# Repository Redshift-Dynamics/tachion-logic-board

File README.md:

The project is in heavy development, use at your own risk

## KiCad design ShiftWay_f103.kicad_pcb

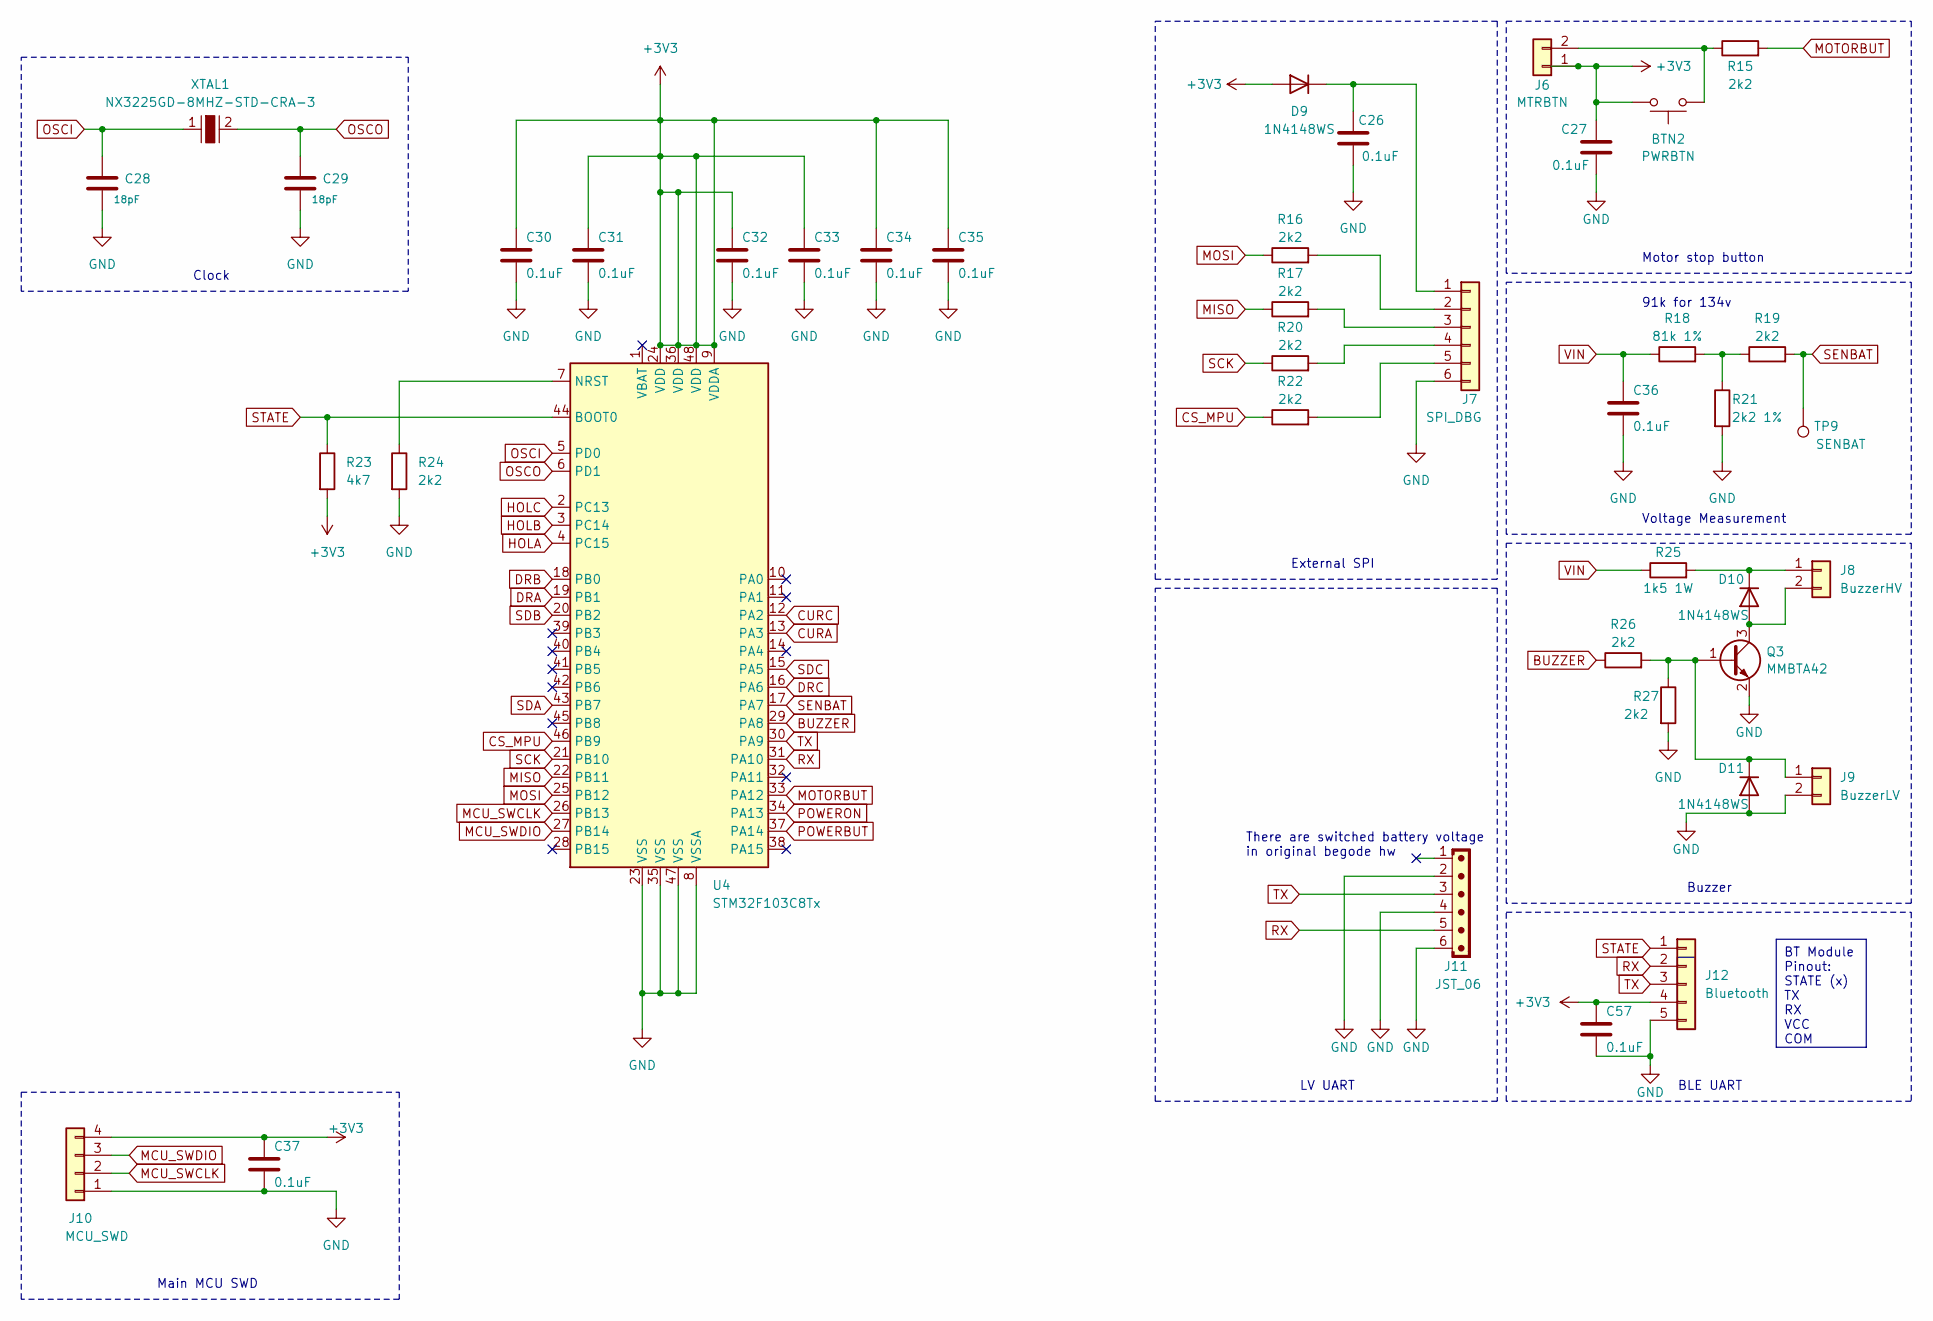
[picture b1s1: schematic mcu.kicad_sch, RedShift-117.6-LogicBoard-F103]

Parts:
BTN2: PWRBTN; SW_SPST_SKQG_WithoutStem
C26, C27, C30, C31, C32, C33, C34, C35, C37, C57: 0.1uF; C_0603_1608Metric_Pad1.08x0.95mm_HandSolder
C28, C29: 18pF; C_0402_1005Metric_Pad0.74x0.62mm_HandSolder
C36: 0.1uF; C_0805_2012Metric_Pad1.18x1.45mm_HandSolder
D9, D10, D11: 1N4148WS; D_SOD-323
J6: MTRBTN; JST_XH_B2B-XH-A_1x02_P2.50mm_Vertical
J7: SPI_DBG; PinSocket_1x07_P1.27mm_Vertical
J8: BuzzerHV; JST_XH_B2B-XH-A_1x02_P2.50mm_Vertical
J9: BuzzerLV; JST_XH_B2B-XH-A_1x02_P2.50mm_Vertical
J10: MCU_SWD; PinSocket_1x04_P2.54mm_Vertical
J11: JST_06; JST_EH_B6B-EH-A_1x06_P2.50mm_Vertical
J12: Bluetooth; PinSocket_1x05_P2.54mm_Vertical
Q3: MMBTA42; SOT-23
R15, R16, R17, R19, R20, R22, R24, R26, R27: 2k2; R_0603_1608Metric_Pad0.98x0.95mm_HandSolder
R18: 81k 1%; R_0805_2012Metric_Pad1.20x1.40mm_HandSolder
R21: 2k2 1%; R_0805_2012Metric_Pad1.20x1.40mm_HandSolder
R23: 4k7; R_0603_1608Metric_Pad0.98x0.95mm_HandSolder
R25: 1k5 1W; R_2010_5025Metric_Pad1.40x2.65mm_HandSolder
TP9: SENBAT; TestPoint_Pad_D2.0mm
U4: STM32F103C8Tx; LQFP-48_7x7mm_P0.5mm
XTAL1: NX3225GD-8MHZ-STD-CRA-3; SMD-2_3.2x2.5mm; MPN NX3225GD-8MHZ-STD-CRA-3; Digi-Key_PN 644-1178-1-ND

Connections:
+3V3: BTN2.2, C27.1, C30.1, C31.1, C32.1, C33.1, C34.1, C35.1, C37.1, C57.1, D9.2 (A), J6.1, J10.4, J12.4, R23.2, U4.9 (VDDA), U4.24 (VDD), U4.36 (VDD), U4.48 (VDD); also elsewhere on the board
BUZZER: R26.1, U4.29 (PA8)
CS_MPU: R22.1, U4.46 (PB9); also elsewhere on the board
CURA: U4.13 (PA3); also elsewhere on the board
CURC: U4.12 (PA2); also elsewhere on the board
DRA: U4.19 (PB1); also elsewhere on the board
DRB: U4.18 (PB0); also elsewhere on the board
DRC: U4.16 (PA6); also elsewhere on the board
GND: C26.2, C27.2, C28.2, C29.2, C30.2, C31.2, C32.2, C33.2, C34.2, C35.2, C36.2, C37.2, C57.2, D11.2 (A), J7.6, J9.2, J10.1, J11.2, J11.4, J11.6, J12.5, Q3.2 (E), R21.2, R24.2, R27.2, U4.8 (VSSA), U4.23 (VSS), U4.35 (VSS), U4.47 (VSS); also elsewhere on the board
HOLA: U4.4 (PC15); also elsewhere on the board
HOLB: U4.3 (PC14); also elsewhere on the board
HOLC: U4.2 (PC13); also elsewhere on the board
MCU_SWCLK: J10.2, U4.26 (PB13)
MCU_SWDIO: J10.3, U4.27 (PB14)
MISO: R17.1, U4.22 (PB11); also elsewhere on the board
MOSI: R16.1, U4.25 (PB12); also elsewhere on the board
MOTORBUT: R15.2, U4.33 (PA12)
unnamed: C26.1, D9.1 (K), J7.1
unnamed: D10.2 (A), J8.2, Q3.3 (C)
unnamed: D10.1 (K), J8.1, R25.2
unnamed: D11.1 (K), J9.1, Q3.1 (B), R26.2, R27.1
unnamed: BTN2.1, J6.2, R15.1
unnamed: J7.2, R16.2
unnamed: J7.3, R17.2
unnamed: J7.4, R20.2
unnamed: J7.5, R22.2
unnamed: R18.2, R19.1, R21.1
unnamed: R24.1, U4.7 (NRST)
OSCI: C28.1, U4.5 (PD0), XTAL1.1
OSCO: C29.1, U4.6 (PD1), XTAL1.2
POWERBUT: U4.37 (PA14); also elsewhere on the board
POWERON: U4.34 (PA13); also elsewhere on the board
RX: J11.5, J12.2, U4.31 (PA10)
SCK: R20.1, U4.21 (PB10); also elsewhere on the board
SDA: U4.43 (PB7); also elsewhere on the board
SDB: U4.20 (PB2); also elsewhere on the board
SDC: U4.15 (PA5); also elsewhere on the board
SENBAT: R19.2, TP9.1, U4.17 (PA7)
STATE: J12.1, R23.1, U4.44 (BOOT0)
TX: J11.3, J12.3, U4.30 (PA9)
VIN: C36.1, R18.1, R25.1; also elsewhere on the board

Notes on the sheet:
BT Module Pinout: STATE (x) TX RX VCC COM
Motor stop button
Clock
External SPI
Main MCU SWD
Buzzer
BLE UART
91k for 134v
Voltage Measurement
There are switched battery voltage in original begode hw
LV UART

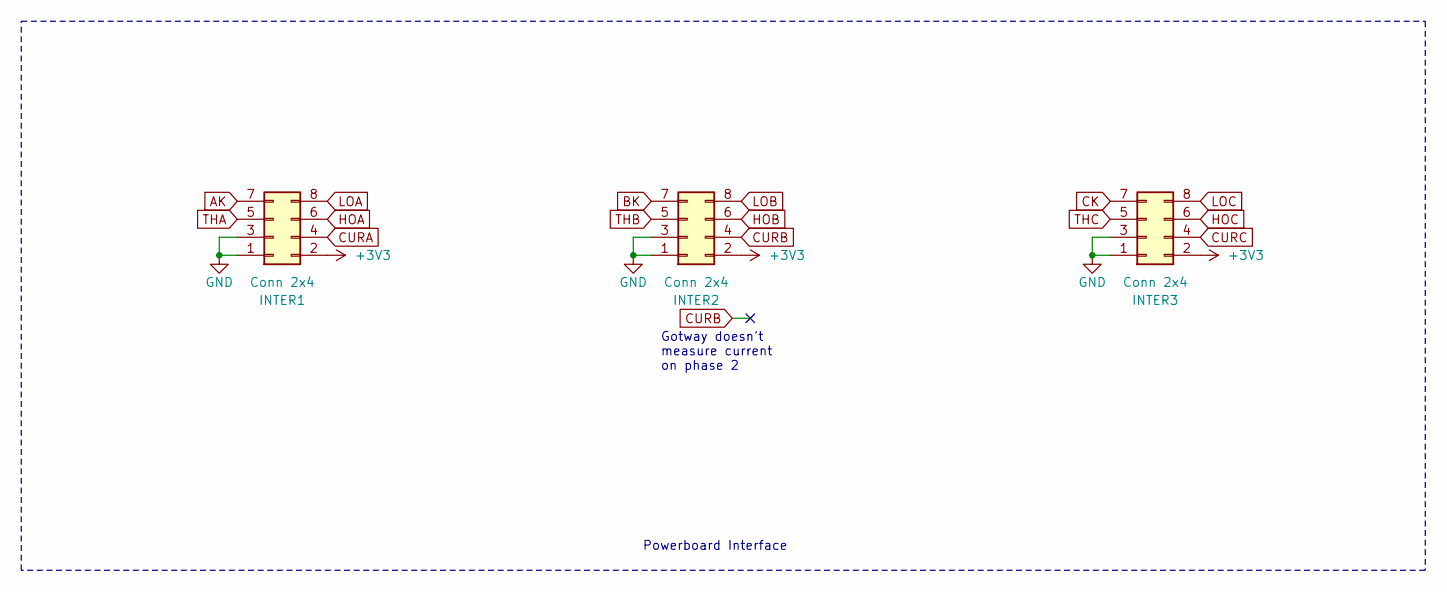
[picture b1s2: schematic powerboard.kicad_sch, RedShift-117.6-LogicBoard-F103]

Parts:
INTER1, INTER2, INTER3: Conn 2x4; PinHeader_2x04_P2.54mm_Vertical

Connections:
+3V3: INTER1.2, INTER2.2, INTER3.2; also elsewhere on the board
AK: INTER1.7; also elsewhere on the board
BK: INTER2.7; also elsewhere on the board
CK: INTER3.7; also elsewhere on the board
CURA: INTER1.4; also elsewhere on the board
CURB: INTER2.4
CURC: INTER3.4; also elsewhere on the board
GND: INTER1.1, INTER1.3, INTER2.1, INTER2.3, INTER3.1, INTER3.3; also elsewhere on the board
HOA: INTER1.6; also elsewhere on the board
HOB: INTER2.6; also elsewhere on the board
HOC: INTER3.6; also elsewhere on the board
LOA: INTER1.8; also elsewhere on the board
LOB: INTER2.8; also elsewhere on the board
LOC: INTER3.8; also elsewhere on the board
THA: INTER1.5
THB: INTER2.5
THC: INTER3.5

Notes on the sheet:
Gotway doesn't measure current on phase 2
Powerboard Interface

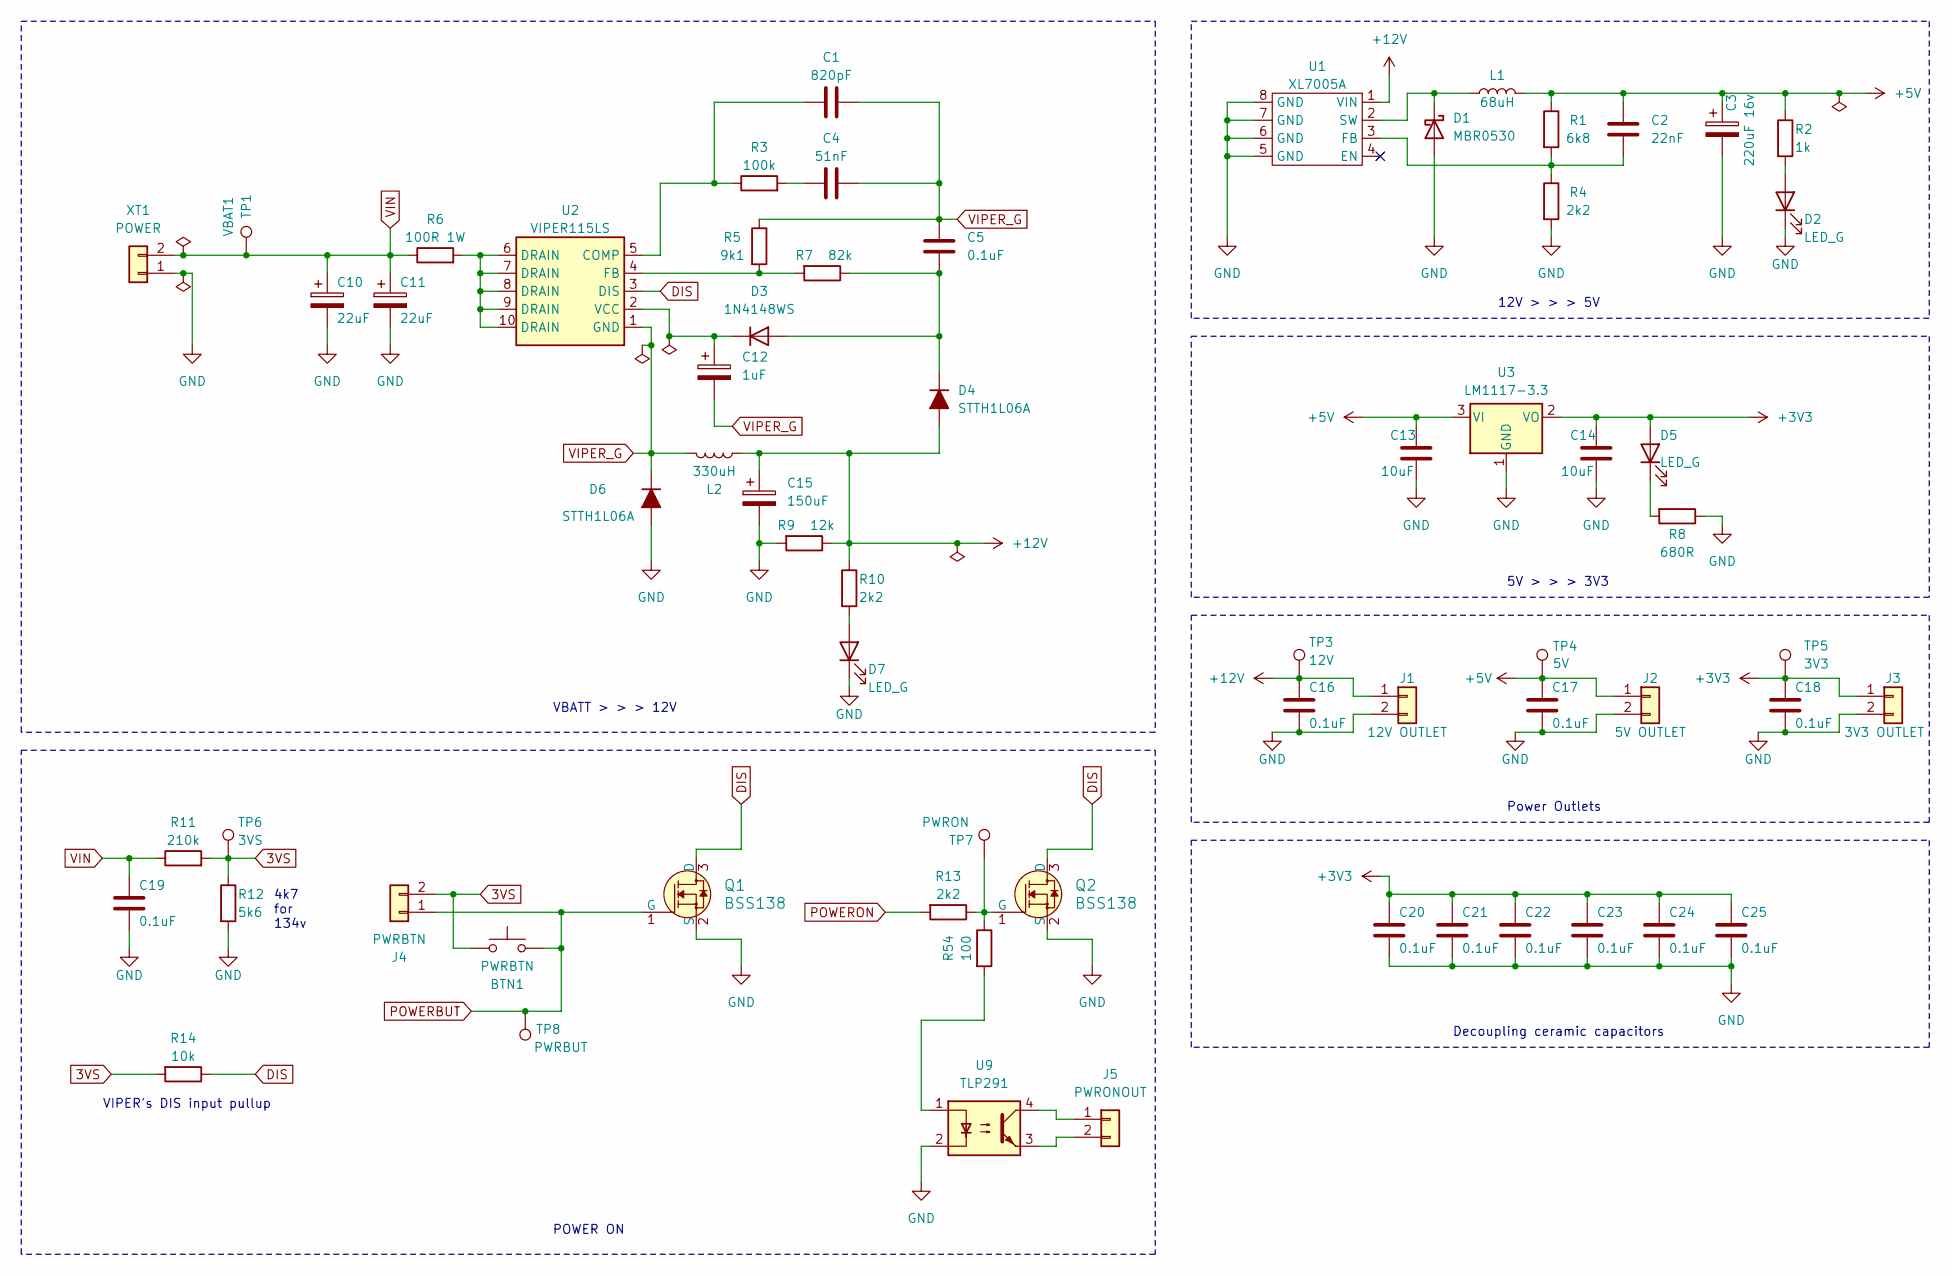
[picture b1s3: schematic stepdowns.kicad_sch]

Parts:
BTN1: PWRBTN; SW_SPST_SKQG_WithoutStem
C1: 820pF; C_0603_1608Metric_Pad1.08x0.95mm_HandSolder
C2: 22nF; C_0603_1608Metric_Pad1.08x0.95mm_HandSolder
C3: 220uF 16v; CP_Elec_6.3x7.7
C4: 51nF; C_0603_1608Metric_Pad1.08x0.95mm_HandSolder
C5, C16, C17, C18, C20, C21, C22, C23, C24, C25: 0.1uF; C_0603_1608Metric_Pad1.08x0.95mm_HandSolder
C10, C11: 22uF; CP_Elec_10x10
C12: 1uF; CP_Elec_10x10
C13, C14: 10uF; C_0603_1608Metric_Pad1.08x0.95mm_HandSolder
C15: 150uF; CP_Elec_10x10
C19: 0.1uF; C_0805_2012Metric_Pad1.18x1.45mm_HandSolder
D1: MBR0530; D_SOD-123
D2, D5, D7: LED_G; LED_0603_1608Metric
D3: 1N4148WS; D_SOD-323
D4, D6: STTH1L06A; D_SMA_Handsoldering
J1: 12V OUTLET; JST_XH_B2B-XH-A_1x02_P2.50mm_Vertical
J2: 5V OUTLET; JST_XH_B2B-XH-A_1x02_P2.50mm_Vertical
J3: 3V3 OUTLET; JST_XH_B2B-XH-A_1x02_P2.50mm_Vertical
J4: PWRBTN; JST_XH_B2B-XH-A_1x02_P2.50mm_Vertical
J5: PWRONOUT; JST_XH_B2B-XH-A_1x02_P2.50mm_Vertical
L1: 68uH; L_Bourns_SRP7028A_7.3x6.6mm
L2: 330uH; L_Bourns_SRR1208_12.7x12.7mm
Q1, Q2: BSS138; SOT-23-3; MPN BSS138; Digi-Key_PN BSS138CT-ND
R1: 6k8; R_0603_1608Metric_Pad0.98x0.95mm_HandSolder
R2: 1k; R_0603_1608Metric_Pad0.98x0.95mm_HandSolder
R3: 100k; R_0603_1608Metric_Pad0.98x0.95mm_HandSolder
R4, R10, R13: 2k2; R_0603_1608Metric_Pad0.98x0.95mm_HandSolder
R5: 9k1; R_0603_1608Metric_Pad0.98x0.95mm_HandSolder
R6: 100R 1W; R_2010_5025Metric_Pad1.40x2.65mm_HandSolder
R7: 82k; R_0603_1608Metric_Pad0.98x0.95mm_HandSolder
R8: 680R; R_0603_1608Metric_Pad0.98x0.95mm_HandSolder
R9: 12k; R_0603_1608Metric_Pad0.98x0.95mm_HandSolder
R11: 210k; R_0805_2012Metric_Pad1.20x1.40mm_HandSolder
R12: 5k6; R_0805_2012Metric_Pad1.20x1.40mm_HandSolder
R14: 10k; R_0603_1608Metric_Pad0.98x0.95mm_HandSolder
R54: 100; R_0603_1608Metric_Pad0.98x0.95mm_HandSolder
TP1: VBAT1; TestPoint_Pad_D2.0mm
TP3: 12V; TestPoint_Pad_D2.0mm
TP4: 5V; TestPoint_Pad_D2.0mm
TP5: 3V3; TestPoint_Pad_D2.0mm
TP6: 3VS; TestPoint_Pad_D2.0mm
TP7: PWRON; TestPoint_Pad_D2.0mm
TP8: PWRBUT; TestPoint_Pad_D2.0mm
U1: XL7005A; SOP-8_3.9x4.9mm_P1.27mm
U2: VIPER115LS; SOIC100P600X175-10N
U3: LM1117-3.3; SOT-223
U9: TLP291; SOIC-4_4.55x2.6mm_P1.27mm
XT1: POWER; AMASS_XT30PW-M_1x02_P2.50mm_Horizontal

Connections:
3VS: BTN1.1, J4.2, R11.2, R12.1, R14.2, TP6.1
+3V3: C14.1, C18.1, C20.1, C21.1, C22.1, C23.1, C24.1, C25.1, D5.2 (A), J3.1, TP5.1, U3.2 (VO); also elsewhere on the board
+5V: C2.1, C3.1, C13.1, C17.1, J2.1, L1.2, R1.1, R2.1, TP4.1, U3.3 (VI); also elsewhere on the board
+12V: C15.1, C16.1, D4.2 (A), J1.1, L2.2, R9.1, R10.1, TP3.1, U1.1 (VIN); also elsewhere on the board
DIS: Q1.3 (D), Q2.3 (D), R14.1, U2.3 (DIS)
GND: C3.2, C10.2, C11.2, C13.2, C14.2, C15.2, C16.2, C17.2, C18.2, C19.2, C20.2, C21.2, C22.2, C23.2, C24.2, C25.2, D1.2 (A), D2.1 (K), D6.2 (A), D7.1 (K), J1.2, J2.2, J3.2, Q1.2 (S), Q2.2 (S), R4.2, R8.1, R9.2, R12.2, U1.5 (GND), U1.6 (GND), U1.7 (GND), U1.8 (GND), U3.1 (GND), U9.2, XT1.1; also elsewhere on the board
unnamed: C4.1, R3.2
unnamed: D1.1 (K), L1.1, U1.2 (SW)
unnamed: D2.2 (A), R2.2
unnamed: C5.1, D3.2 (A), D4.1 (K), R7.1
unnamed: C12.1, D3.1 (K), U2.2 (VCC)
unnamed: D5.1 (K), R8.2
unnamed: D7.2 (A), R10.2
unnamed: J5.1, U9.4
unnamed: J5.2, U9.3
unnamed: Q2.1 (G), R13.1, R54.1, TP7.1
unnamed: R6.2, U2.6 (DRAIN), U2.7 (DRAIN), U2.8 (DRAIN), U2.9 (DRAIN), U2.10 (DRAIN)
unnamed: R54.2, U9.1
unnamed: C2.2, R1.2, R4.1, U1.3 (FB)
unnamed: C1.1, R3.1, U2.5 (COMP)
unnamed: R5.2, R7.2, U2.4 (FB)
POWERBUT: BTN1.2, J4.1, Q1.1 (G), TP8.1; also elsewhere on the board
POWERON: R13.2; also elsewhere on the board
VIN: C10.1, C11.1, C19.1, R6.1, R11.1, TP1.1, XT1.2; also elsewhere on the board
VIPER_G: C1.2, C4.2, C5.2, C12.2, D6.1 (K), L2.1, R5.1, U2.1 (GND)

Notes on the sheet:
Decoupling ceramic capacitors
VBATT > > > 12V
5V > > > 3V3
4k7 for 134v
Power Outlets
12V > > > 5V
POWER ON
VIPER's DIS input pullup

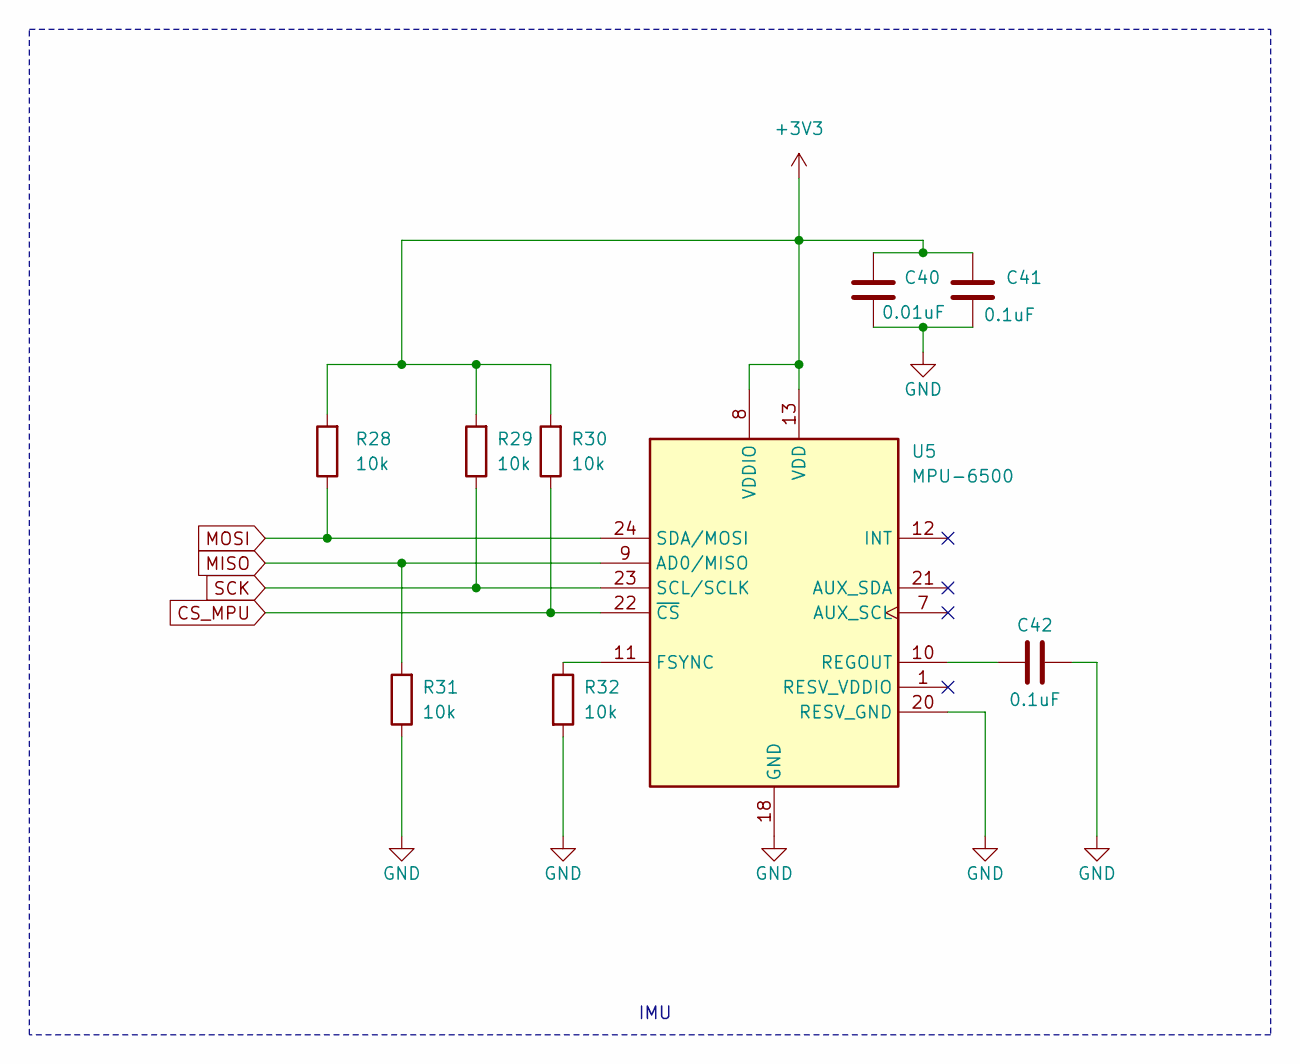
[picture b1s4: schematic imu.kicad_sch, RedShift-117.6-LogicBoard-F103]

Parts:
C40: 0.01uF; C_0603_1608Metric_Pad1.08x0.95mm_HandSolder
C41, C42: 0.1uF; C_0603_1608Metric_Pad1.08x0.95mm_HandSolder
R28, R29, R30, R31, R32: 10k; R_0603_1608Metric_Pad0.98x0.95mm_HandSolder
U5: MPU-6500; InvenSense_QFN-24_3x3mm_P0.4mm

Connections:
+3V3: C40.1, C41.1, R28.2, R29.2, R30.2, U5.8 (VDDIO), U5.13 (VDD); also elsewhere on the board
CS_MPU: R30.1, U5.22 (~CS); also elsewhere on the board
GND: C40.2, C41.2, C42.1, R31.1, R32.2, U5.18 (GND), U5.20 (RESV_GND); also elsewhere on the board
MISO: R31.2, U5.9 (AD0/MISO); also elsewhere on the board
MOSI: R28.1, U5.24 (SDA/MOSI); also elsewhere on the board
unnamed: R32.1, U5.11 (FSYNC)
unnamed: C42.2, U5.10 (REGOUT)
SCK: R29.1, U5.23 (SCL/SCLK); also elsewhere on the board

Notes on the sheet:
IMU

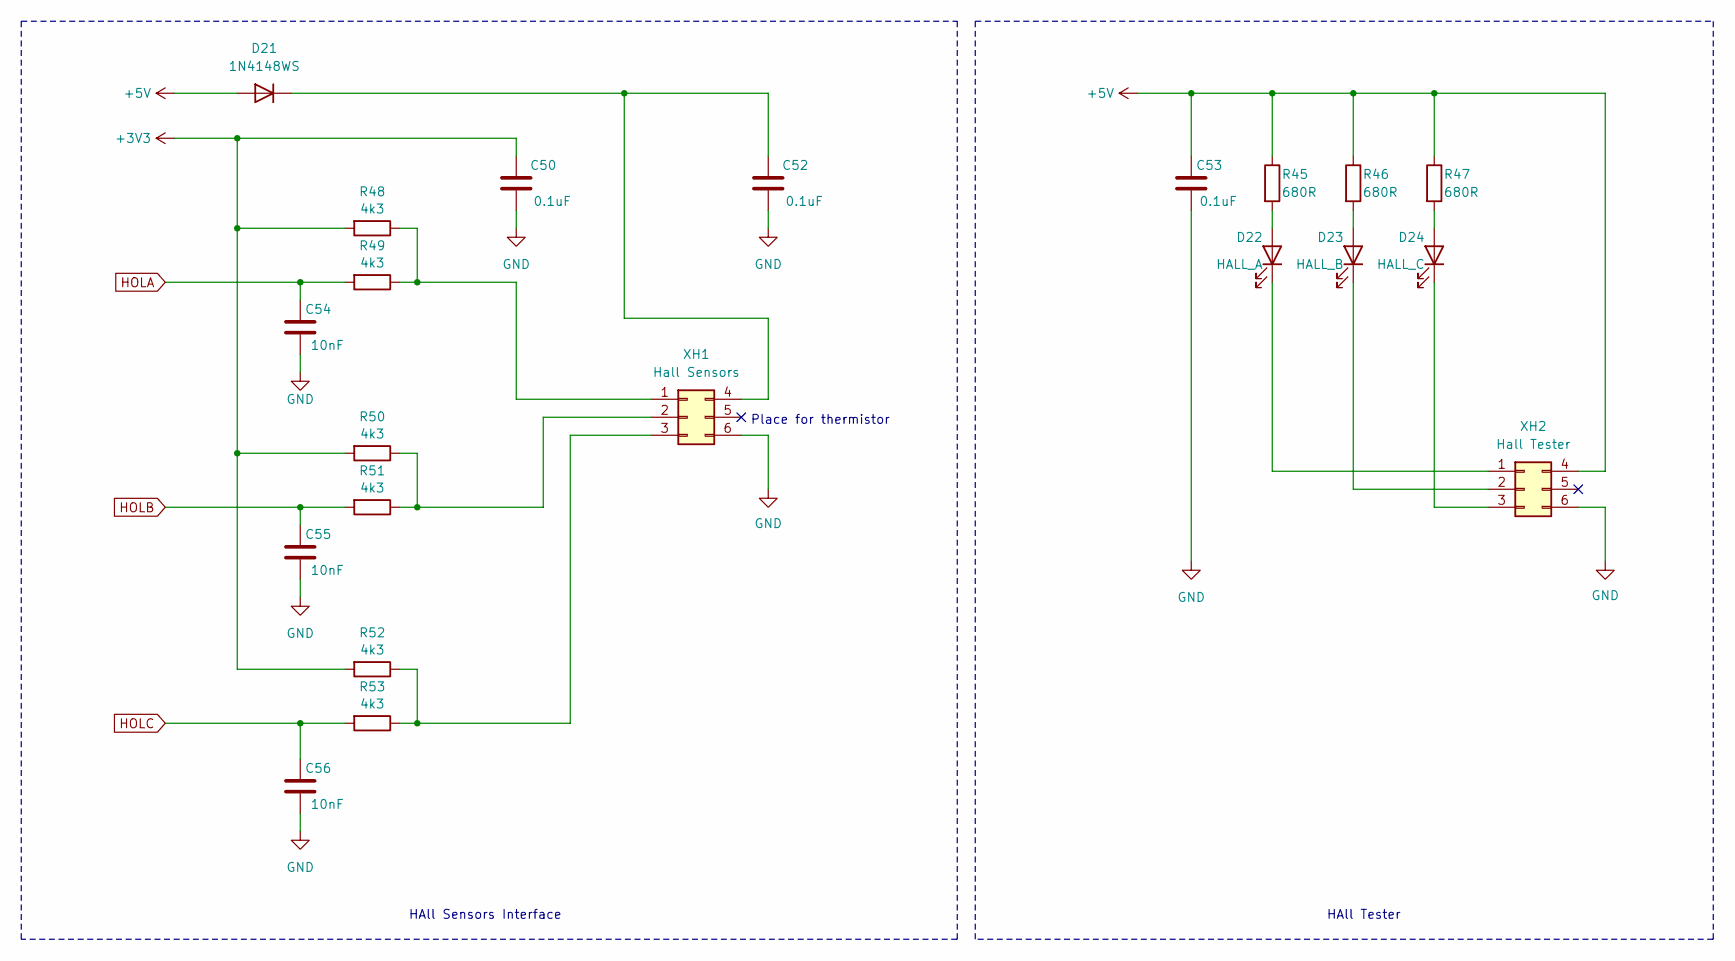
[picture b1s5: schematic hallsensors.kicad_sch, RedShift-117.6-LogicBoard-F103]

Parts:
C50, C52, C53: 0.1uF; C_0603_1608Metric_Pad1.08x0.95mm_HandSolder
C54, C55, C56: 10nF; C_0603_1608Metric_Pad1.08x0.95mm_HandSolder
D21: 1N4148WS; D_SOD-323
D22: HALL_A; LED_0603_1608Metric
D23: HALL_B; LED_0603_1608Metric
D24: HALL_C; LED_0603_1608Metric
R45, R46, R47: 680R; R_0603_1608Metric_Pad0.98x0.95mm_HandSolder
R48, R49, R50, R51, R52, R53: 4k3; R_0603_1608Metric_Pad0.98x0.95mm_HandSolder
XH1: Hall Sensors; Molex_Micro-Fit_3.0_43045-0600_2x03_P3.00mm_Horizontal
XH2: Hall Tester; Molex_Micro-Fit_3.0_43045-0600_2x03_P3.00mm_Horizontal

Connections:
+3V3: C50.1, R48.2, R50.2, R52.2; also elsewhere on the board
+5V: C53.1, D21.2 (A), R45.1, R46.1, R47.1, XH2.4; also elsewhere on the board
GND: C50.2, C52.2, C53.2, C54.2, C55.2, C56.2, XH1.6, XH2.6; also elsewhere on the board
HOLA: C54.1, R49.2; also elsewhere on the board
HOLB: C55.1, R51.2; also elsewhere on the board
HOLC: C56.1, R53.2; also elsewhere on the board
unnamed: C52.1, D21.1 (K), XH1.4
unnamed: D22.2 (A), R45.2
unnamed: D22.1 (K), XH2.1
unnamed: D23.2 (A), R46.2
unnamed: D23.1 (K), XH2.2
unnamed: D24.2 (A), R47.2
unnamed: D24.1 (K), XH2.3
unnamed: R48.1, R49.1, XH1.1
unnamed: R50.1, R51.1, XH1.2
unnamed: R52.1, R53.1, XH1.3

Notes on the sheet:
Place for thermistor
HAll Tester
HAll Sensors Interface

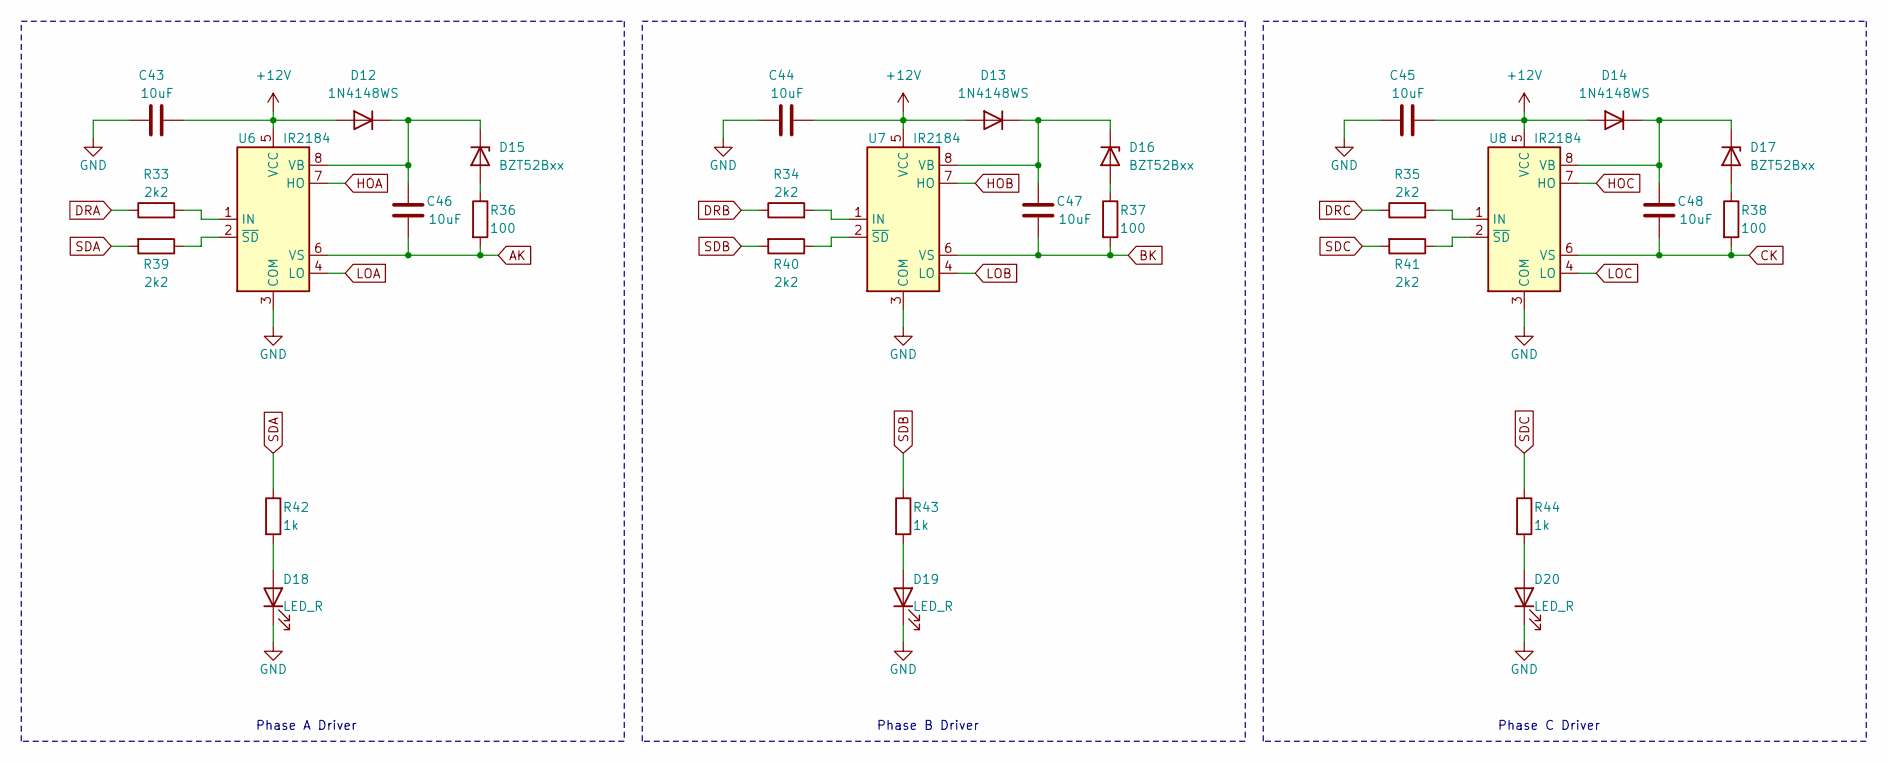
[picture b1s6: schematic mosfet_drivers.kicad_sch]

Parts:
C43, C44, C45, C46, C47, C48: 10uF; C_0603_1608Metric_Pad1.08x0.95mm_HandSolder
D12, D13, D14: 1N4148WS; D_SOD-323
D15, D16, D17: BZT52Bxx; D_SOD-123F
D18, D19, D20: LED_R; LED_0603_1608Metric
R33, R34, R35, R39, R40, R41: 2k2; R_0603_1608Metric_Pad0.98x0.95mm_HandSolder
R36, R37, R38: 100; R_0603_1608Metric_Pad0.98x0.95mm_HandSolder
R42, R43, R44: 1k; R_0603_1608Metric_Pad0.98x0.95mm_HandSolder
U6, U7, U8: IR2184; SOIC-8-1EP_3.9x4.9mm_P1.27mm_EP2.514x3.2mm_ThermalVias

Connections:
+12V: C43.2, C44.2, C45.2, D12.2 (A), D13.2 (A), D14.2 (A), U6.5 (VCC), U7.5 (VCC), U8.5 (VCC); also elsewhere on the board
AK: C46.2, R36.2, U6.6 (VS); also elsewhere on the board
BK: C47.2, R37.2, U7.6 (VS); also elsewhere on the board
CK: C48.2, R38.2, U8.6 (VS); also elsewhere on the board
DRA: R33.1; also elsewhere on the board
DRB: R34.1; also elsewhere on the board
DRC: R35.1; also elsewhere on the board
GND: C43.1, C44.1, C45.1, D18.1 (K), D19.1 (K), D20.1 (K), U6.3 (COM), U7.3 (COM), U8.3 (COM); also elsewhere on the board
HOA: U6.7 (HO); also elsewhere on the board
HOB: U7.7 (HO); also elsewhere on the board
HOC: U8.7 (HO); also elsewhere on the board
LOA: U6.4 (LO); also elsewhere on the board
LOB: U7.4 (LO); also elsewhere on the board
LOC: U8.4 (LO); also elsewhere on the board
unnamed: C46.1, D12.1 (K), D15.1 (K), U6.8 (VB)
unnamed: C47.1, D13.1 (K), D16.1 (K), U7.8 (VB)
unnamed: C48.1, D14.1 (K), D17.1 (K), U8.8 (VB)
unnamed: D15.2 (A), R36.1
unnamed: D16.2 (A), R37.1
unnamed: D17.2 (A), R38.1
unnamed: D18.2 (A), R42.2
unnamed: D19.2 (A), R43.2
unnamed: D20.2 (A), R44.2
unnamed: R33.2, U6.1 (IN)
unnamed: R39.1, U6.2 (~SD)
unnamed: R34.2, U7.1 (IN)
unnamed: R40.1, U7.2 (~SD)
unnamed: R35.2, U8.1 (IN)
unnamed: R41.1, U8.2 (~SD)
SDA: R39.2, R42.1; also elsewhere on the board
SDB: R40.2, R43.1; also elsewhere on the board
SDC: R41.2, R44.1; also elsewhere on the board

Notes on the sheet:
Phase A Driver
Phase B Driver
Phase C Driver

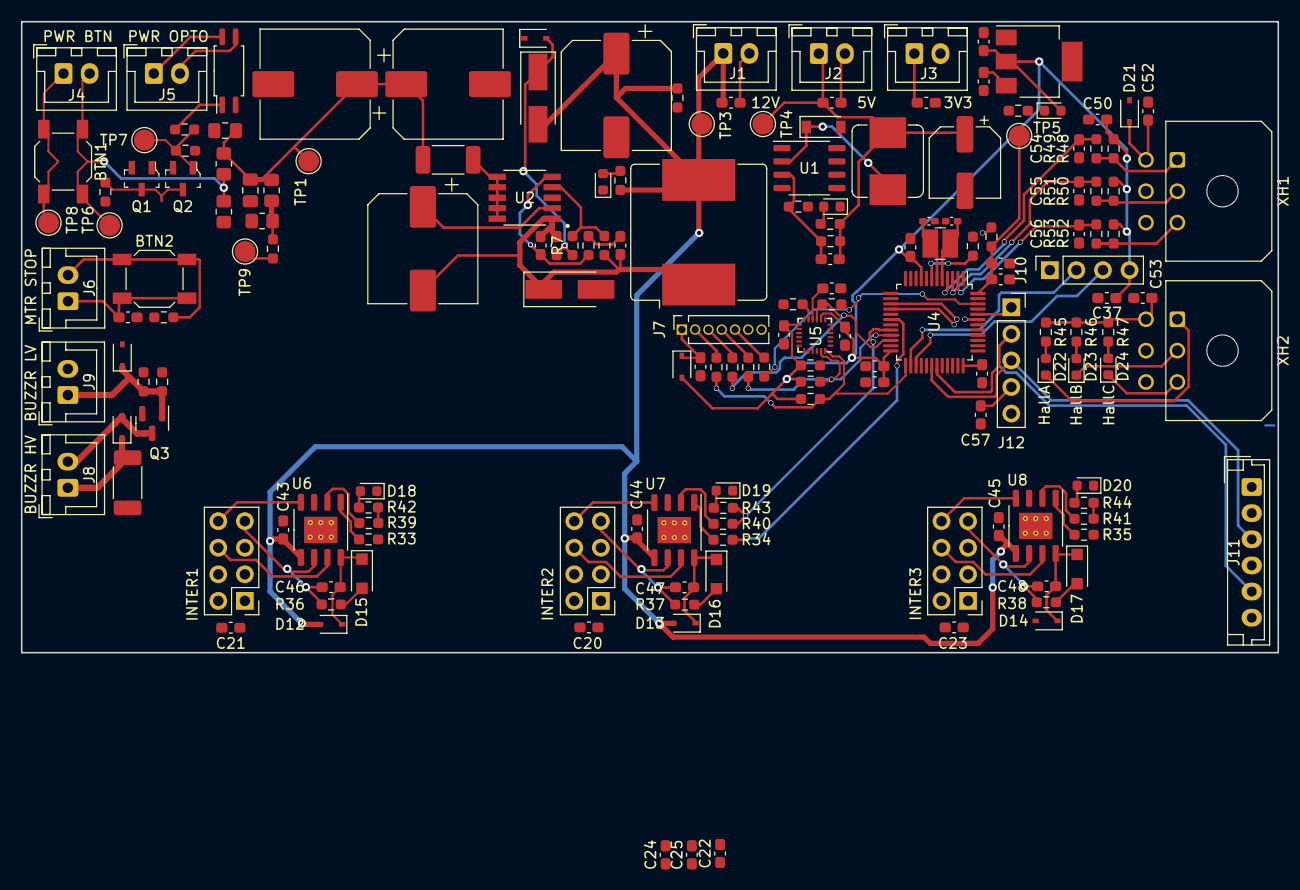
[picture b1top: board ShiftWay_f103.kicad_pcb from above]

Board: 2 copper layers, 120.1 x 60.3 mm, 168 parts (0 on the bottom side), 97 nets.

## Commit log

2023-12-07 Add files via upload
    changed 12v power to ICW6215, added 5 and 3v3
2023-12-07 Add files via upload
    Added hivoltage cirquit. TODO - add powon (VT19 on MSX)
2023-12-07 Add files via upload
    Add +12 and +5 outlets, change buzzer transistor, minor updates
2023-12-07 Divider, gate, mtr button, testpoints, minors
2023-12-07 Minors, annotation
2023-12-08 Add footprints, fixed xtal
2023-12-09 Add files via upload
    Add leds and minors
2023-12-10 fixed some footprints
2023-12-10 Fixed short cirquit, minors
2023-12-11 Fix mistakes
2024-01-05 Add drivers, stepdown on VIPER115, fixes
2024-01-08 topology in progress
2024-02-12 Replaced unused GPIO, added SWD connectorm, PCB in progress
2024-02-19 Fixes, layouting
2024-03-23 removed swd
2024-05-30 Major update on results of testing first order board and on results of crosscheck
    * reworked mainswitch scheme
    * mainswitch divider. expected commutation time - 2us
    * added 3v3bt and 3v3hall
    * tvs on hall
    * divided 5vhall, 3vhall, 3vbt
    * fix misplacement gnd and 3v3 at the BT connector
2024-06-04 Fix pullup IMU, pulldown boot0, vbat before resi
